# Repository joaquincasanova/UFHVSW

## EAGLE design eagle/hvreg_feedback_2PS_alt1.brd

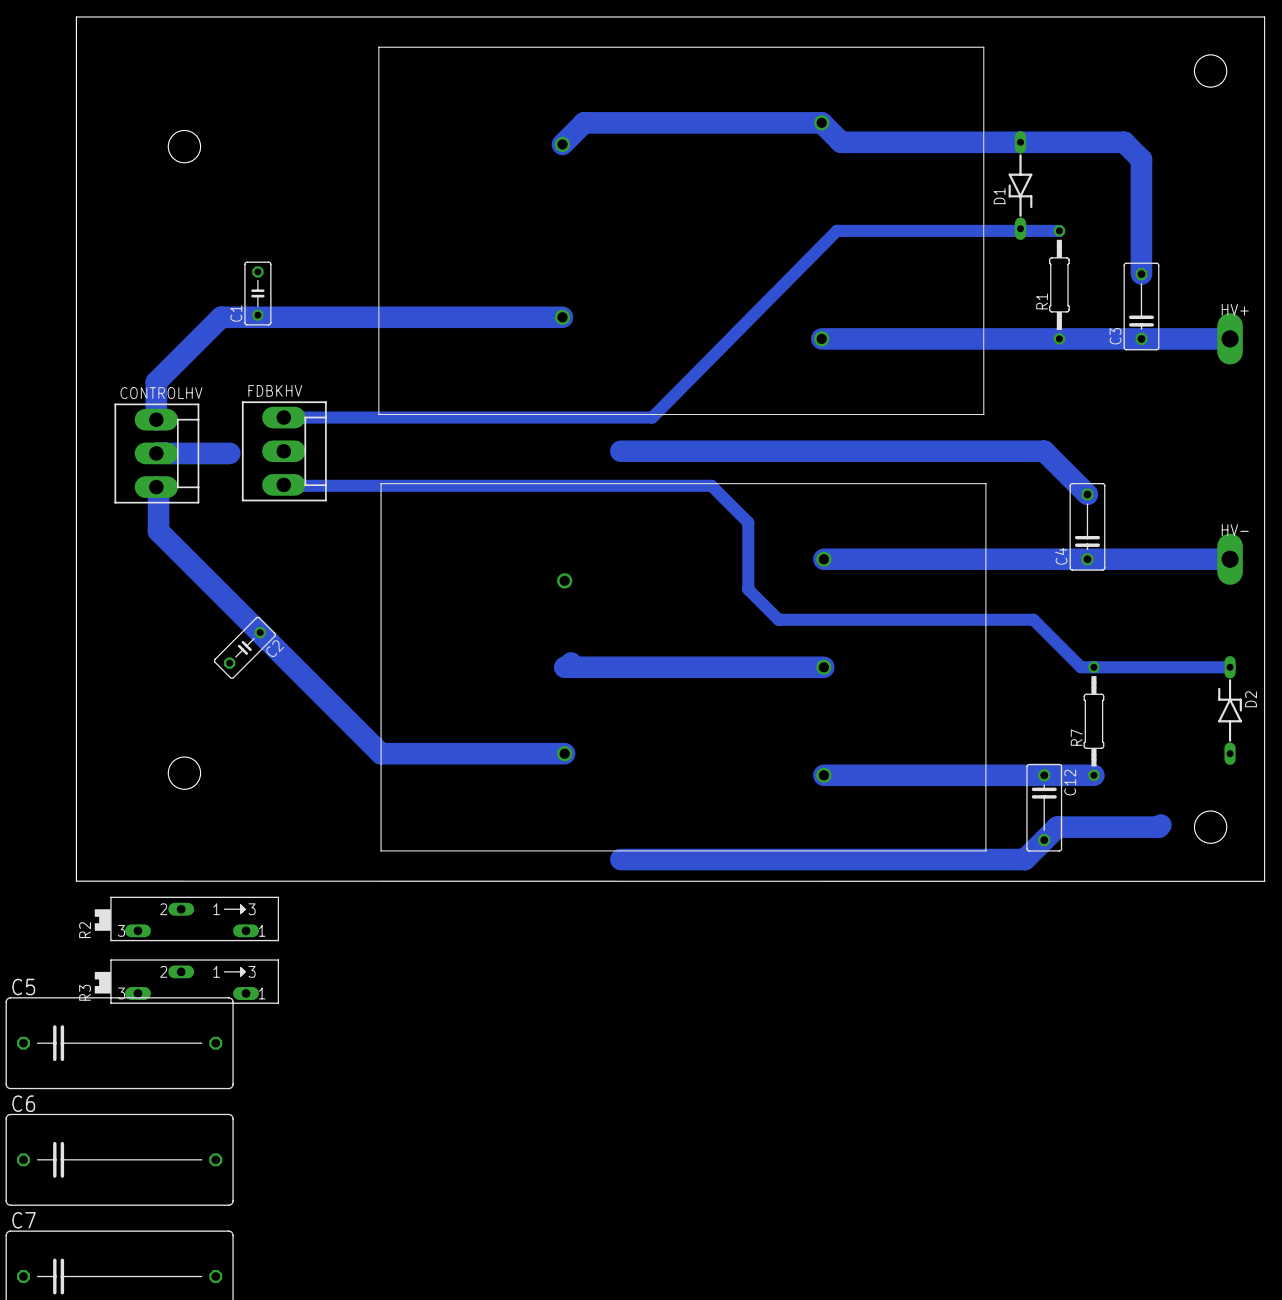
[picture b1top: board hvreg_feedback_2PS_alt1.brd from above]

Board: 2 copper layers, 139.7 x 101.6 mm, 20 parts (0 on the bottom side), 8 nets.

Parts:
C1, C2: C050-030X075
C3, C4, C12: .01u; C075-042X103
C5, C6, C7: 1u; C225-108X268
CONTROLHV: KK-156-3
D1, D2: 1n4733; ZDIO-10
FDBKHV: KK-156-3
HV+: TPPAD1-20Y; P1-20Y
HV-: TPPAD1-20Y; P1-20Y
R1, R7: 2M; 0207/12
R2, R3: SP19L
U$1: EMCO-F104PIN; EMCO-F
U$2: EMCO-F20CT; EMCO-F*CT

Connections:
GND: C1.2, C2.2, C3.2, C4.2, C5.2, C6.2, C7.2, C12.2, CONTROLHV.2, D1.A, D2.A, FDBKHV.2, R2.E, R2.S, R3.E, R3.S, U$1.P$2, U$1.P$4, U$2.P$2, U$2.P$5
unnamed: C3.1, C5.1, HV+.TP, R1.1, U$1.P$3
unnamed: C6.1, C12.1, R7.1, U$2.P$3
unnamed: D1.C, FDBKHV.1, R1.2, R2.A
unnamed: C1.1, CONTROLHV.1, U$1.P$1
unnamed: C2.1, CONTROLHV.3, U$2.P$1
unnamed: C4.1, C7.1, HV-.TP, U$2.P$4
unnamed: D2.C, FDBKHV.3, R3.A, R7.2

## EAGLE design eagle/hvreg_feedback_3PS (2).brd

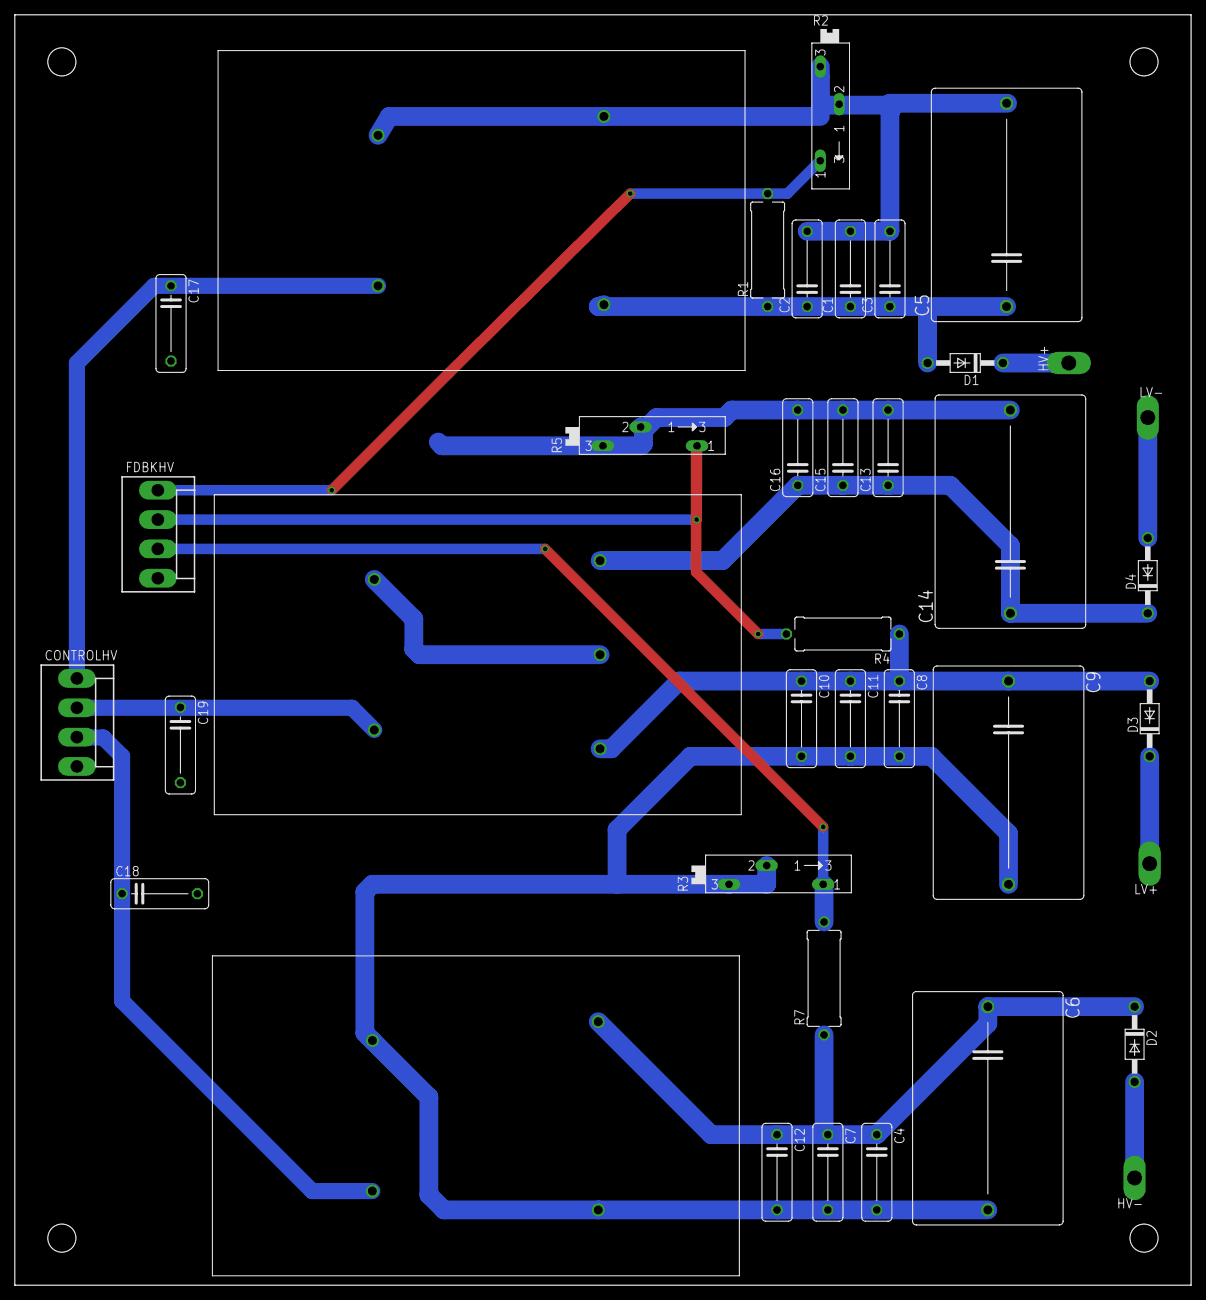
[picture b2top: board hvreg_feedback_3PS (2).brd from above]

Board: 2 copper layers, 158.8 x 171.4 mm, 38 parts (0 on the bottom side), 15 nets.

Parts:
C1, C4, C10, C15: 1n; C102-043X133
C2, C7, C11, C16: 10p; C102-043X133
C3, C8, C12, C13: .01u; C102-043X133
C5, C6, C9, C14: 1u; C275-205X316
C17, C18, C19: .1u; C102-043X133
CONTROLHV: KK-156-4
D1, D2, D3, D4: 1N4004; DO41-10
FDBKHV: KK-156-4
HV+: TPPAD1-20Y; P1-20Y
HV-: TPPAD1-20Y; P1-20Y
LV+: TPPAD1-20Y; P1-20Y
LV-: TPPAD1-20Y; P1-20Y
R1, R4, R7: 2M; P0613/15
R2, R3, R5: SP19L
U$1, U$2: EMCO-F104PIN; EMCO-F
U$3: EMCO-F20CT; EMCO-F*CT

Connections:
GND: C1.2, C2.2, C3.2, C4.2, C5.2, C6.2, C7.2, C8.2, C9.2, C10.2, C11.2, C12.2, C13.2, C14.2, C15.2, C16.2, C17.2, C18.2, C19.2, CONTROLHV.4, FDBKHV.4, R2.E, R2.S, R3.E, R3.S, R5.E, R5.S, U$1.P$2, U$1.P$4, U$2.P$2, U$2.P$3, U$3.P$2, U$3.P$5
unnamed: C1.1, C2.1, C3.1, C5.1, D1.A, R1.1, U$1.P$3
unnamed: C4.1, C6.1, C7.1, C12.1, D2.C, R7.1, U$2.P$4
unnamed: FDBKHV.1, R1.2, R2.A
unnamed: D2.A, HV-.TP
unnamed: C8.1, C9.1, C10.1, C11.1, D3.A, R4.1, U$3.P$3
unnamed: D1.C, HV+.TP
unnamed: FDBKHV.2, R4.2, R5.A
unnamed: FDBKHV.3, R3.A, R7.2
unnamed: D3.C, LV+.TP
unnamed: C13.1, C14.1, C15.1, C16.1, D4.C, U$3.P$4
unnamed: D4.A, LV-.TP
unnamed: C17.1, CONTROLHV.1, U$1.P$1
unnamed: C19.1, CONTROLHV.2, U$3.P$1
unnamed: C18.1, CONTROLHV.3, U$2.P$1

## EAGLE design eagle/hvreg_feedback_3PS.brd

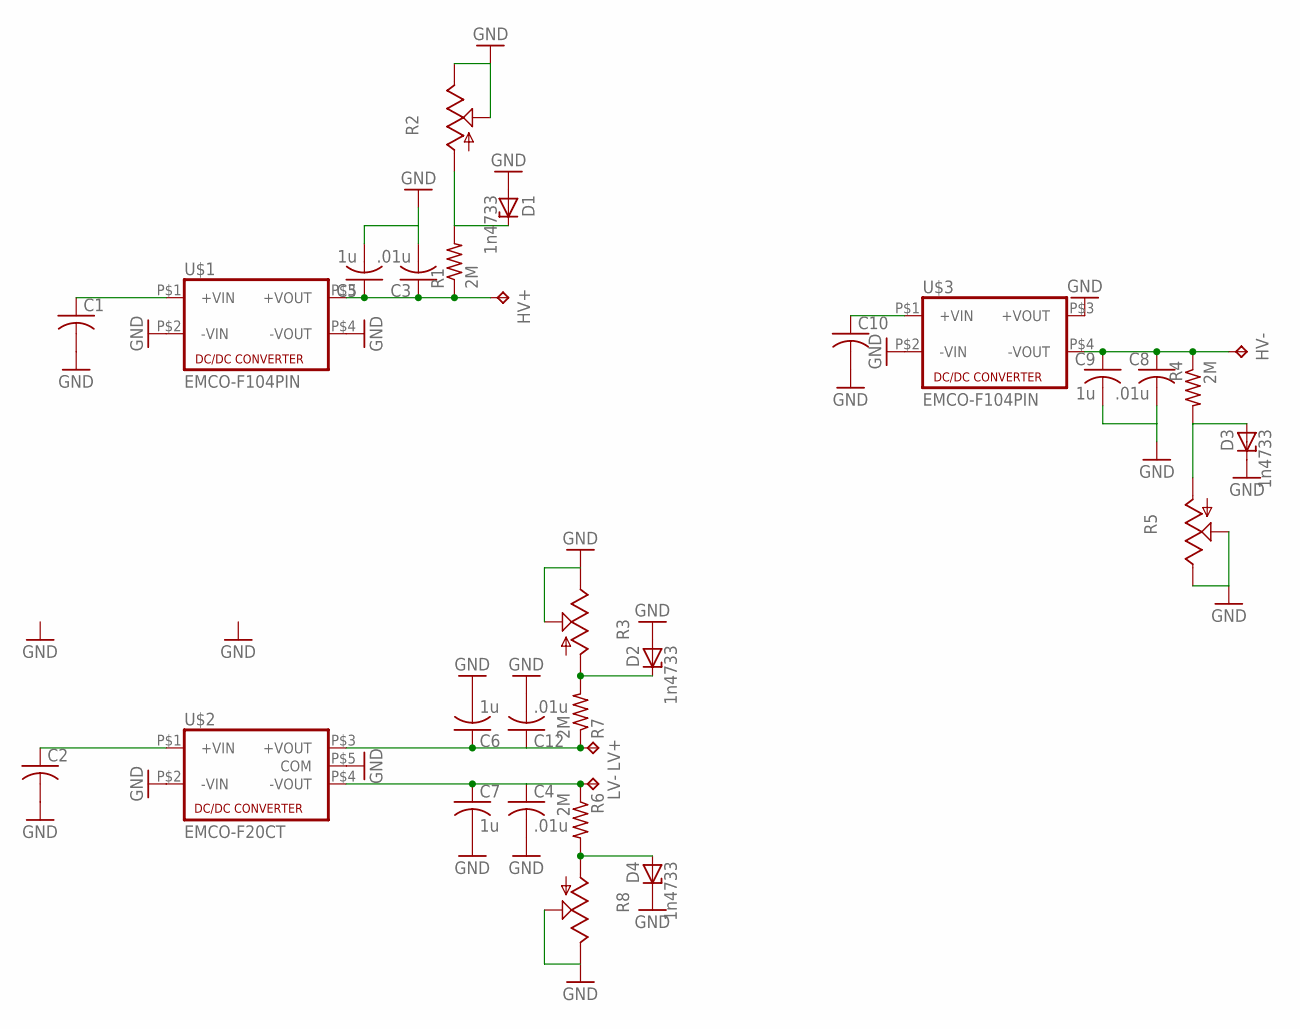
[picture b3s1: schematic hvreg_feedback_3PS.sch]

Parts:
C1, C2, C10: C-US050-030X075; C050-030X075
C3, C4, C8, C12: .01u; C075-042X103
C5, C6, C7, C9: 1u; C225-108X268
D1, D2, D3, D4: 1n4733; ZDIO-10
HV+: TPPAD1-20Y; P1-20Y
HV-: TPPAD1-20Y; P1-20Y
LV+: TPPAD1-20Y; P1-20Y
LV-: TPPAD1-20Y; P1-20Y
R1, R4, R6, R7: 2M; 0207/12
R2, R3, R5, R8: TRIM_US-B90P; SP19L
U$1, U$3: EMCO-F104PIN; EMCO-F
U$2: EMCO-F20CT; EMCO-F*CT

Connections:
GND: C1.2, C2.2, C3.2, C4.2, C5.2, C6.2, C7.2, C8.2, C9.2, C10.2, C12.2, D1.A, D2.A, D3.C, D4.C, R2.E, R2.S, R3.E, R3.S, R5.E, R5.S, R8.E, R8.S, U$1.P$2 (-VIN), U$1.P$4 (-VOUT), U$2.P$2 (-VIN), U$2.P$5 (COM), U$3.P$2 (-VIN), U$3.P$3 (+VOUT)
unnamed: C3.1, C5.1, HV+.TP, R1.1, U$1.P$3 (+VOUT)
unnamed: C6.1, C12.1, LV+.TP, R7.1, U$2.P$3 (+VOUT)
unnamed: D1.C, R1.2, R2.A
unnamed: C1.1, U$1.P$1 (+VIN)
unnamed: C2.1, U$2.P$1 (+VIN)
unnamed: C4.1, C7.1, LV-.TP, R6.1
unnamed: C8.1, C9.1, HV-.TP, R4.1
unnamed: D2.C, R3.A, R7.2
unnamed: D3.A, R4.2, R5.A
unnamed: C10.1, U$3.P$1 (+VIN)
unnamed: D4.A, R6.2, R8.A

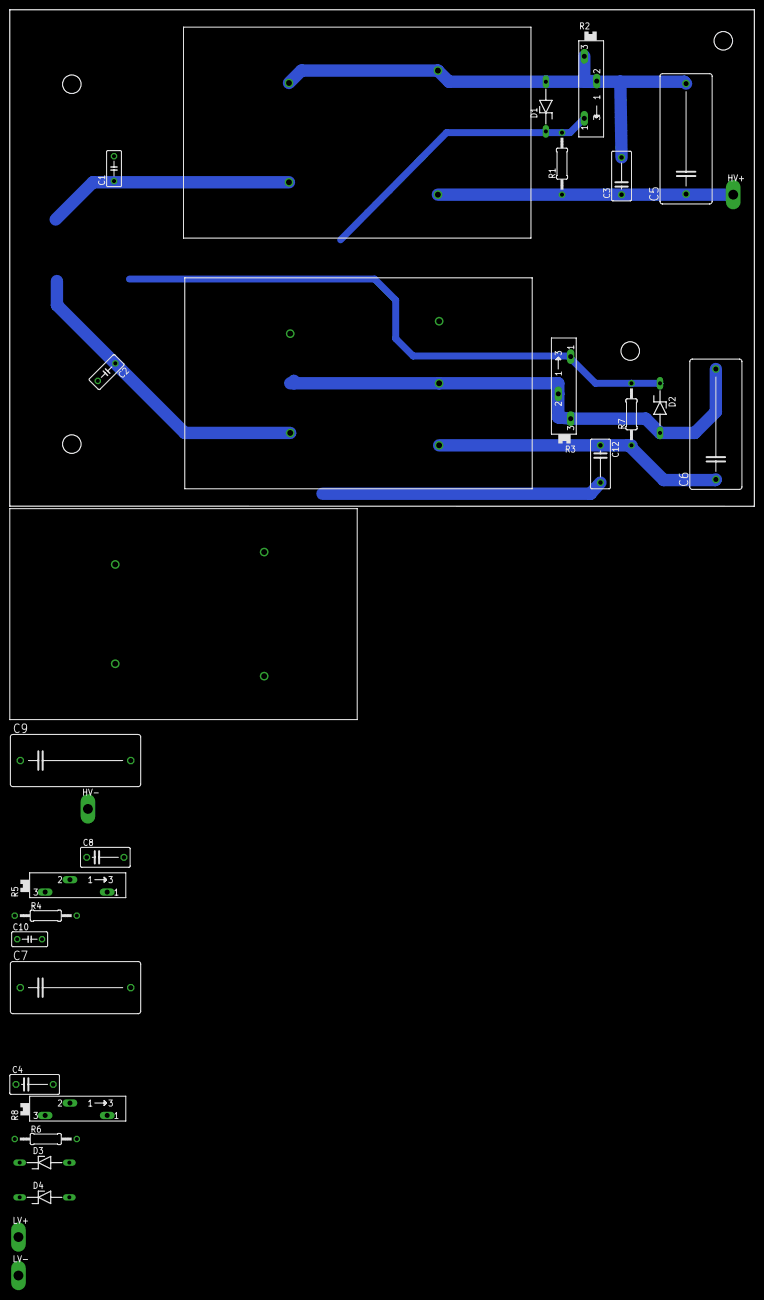
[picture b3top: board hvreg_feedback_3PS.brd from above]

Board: 2 copper layers, 152.4 x 101.6 mm, 30 parts (0 on the bottom side), 12 nets.

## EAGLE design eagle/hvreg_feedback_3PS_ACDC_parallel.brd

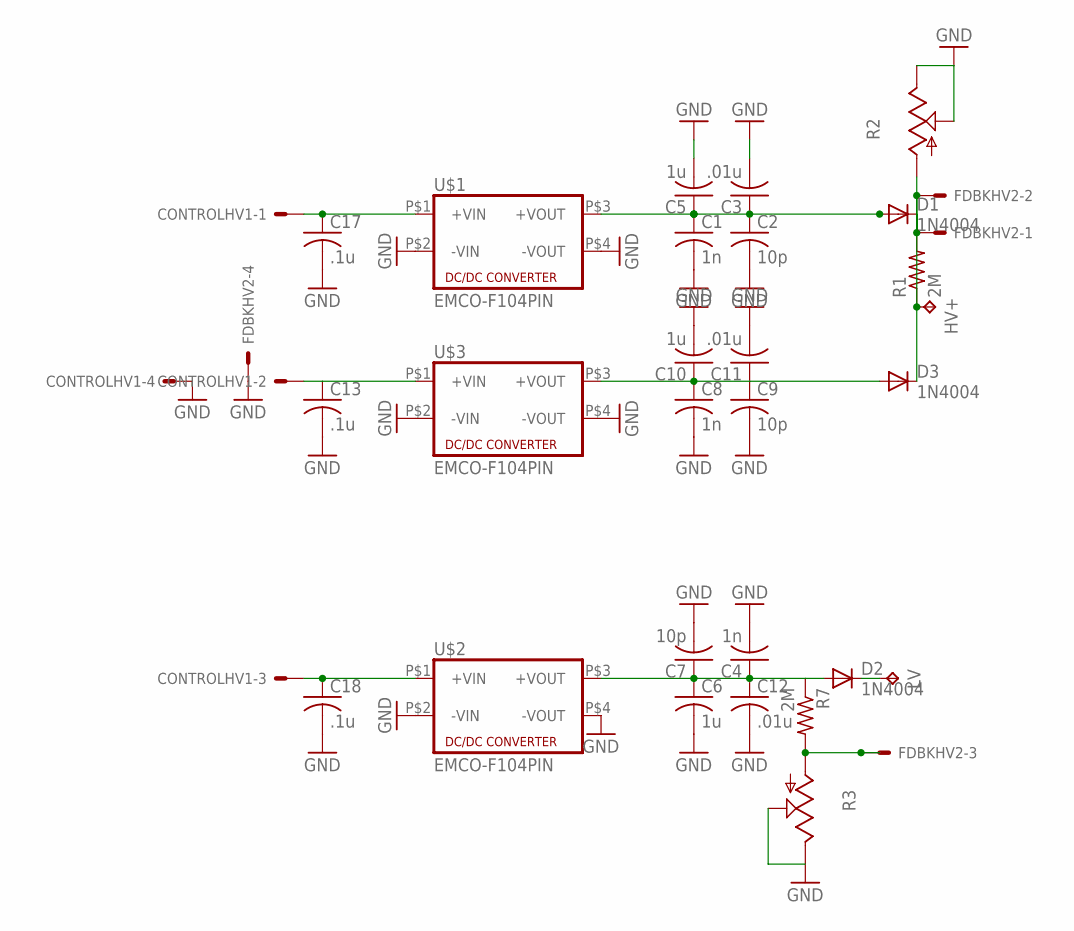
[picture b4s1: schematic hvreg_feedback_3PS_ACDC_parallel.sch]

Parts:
C1, C4, C8: 1n; C102-043X133
C2, C7, C9: 10p; C102-043X133
C3, C11, C12: .01u; C102-043X133
C5, C6, C10: 1u; C275-205X316
C13, C17, C18: .1u; C102-043X133
CONTROLHV1: KK-156-4
D1, D2, D3: 1N4004; DO41-10
FDBKHV2: KK-156-4
HV+: TPPAD1-20Y; P1-20Y
LV: TPPAD1-20Y; P1-20Y
R1, R7: 2M; P0613/15
R2, R3: TRIM_US-B90P; SP19L
U$1, U$2, U$3: EMCO-F104PIN; EMCO-F

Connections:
GND: C1.2, C2.2, C3.2, C4.2, C5.2, C6.2, C7.2, C8.2, C9.2, C10.2, C11.2, C12.2, C13.2, C17.2, C18.2, CONTROLHV1.4, FDBKHV2.4, R2.E, R2.S, R3.E, R3.S, U$1.P$2 (-VIN), U$1.P$4 (-VOUT), U$2.P$2 (-VIN), U$2.P$4 (-VOUT), U$3.P$2 (-VIN), U$3.P$4 (-VOUT)
unnamed: C1.1, C2.1, C3.1, C5.1, D1.A, U$1.P$3 (+VOUT)
unnamed: C4.1, C6.1, C7.1, C12.1, D2.A, R7.1, U$2.P$3 (+VOUT)
unnamed: FDBKHV2.1, FDBKHV2.2, R1.2, R2.A
unnamed: D2.C, LV.TP
unnamed: D1.C, D3.C, HV+.TP, R1.1
unnamed: C8.1, C9.1, C10.1, C11.1, D3.A, U$3.P$3 (+VOUT)
unnamed: FDBKHV2.3, R3.A, R7.2
unnamed: C13.1, CONTROLHV1.2, U$3.P$1 (+VIN)
unnamed: C17.1, CONTROLHV1.1, U$1.P$1 (+VIN)
unnamed: C18.1, CONTROLHV1.3, U$2.P$1 (+VIN)

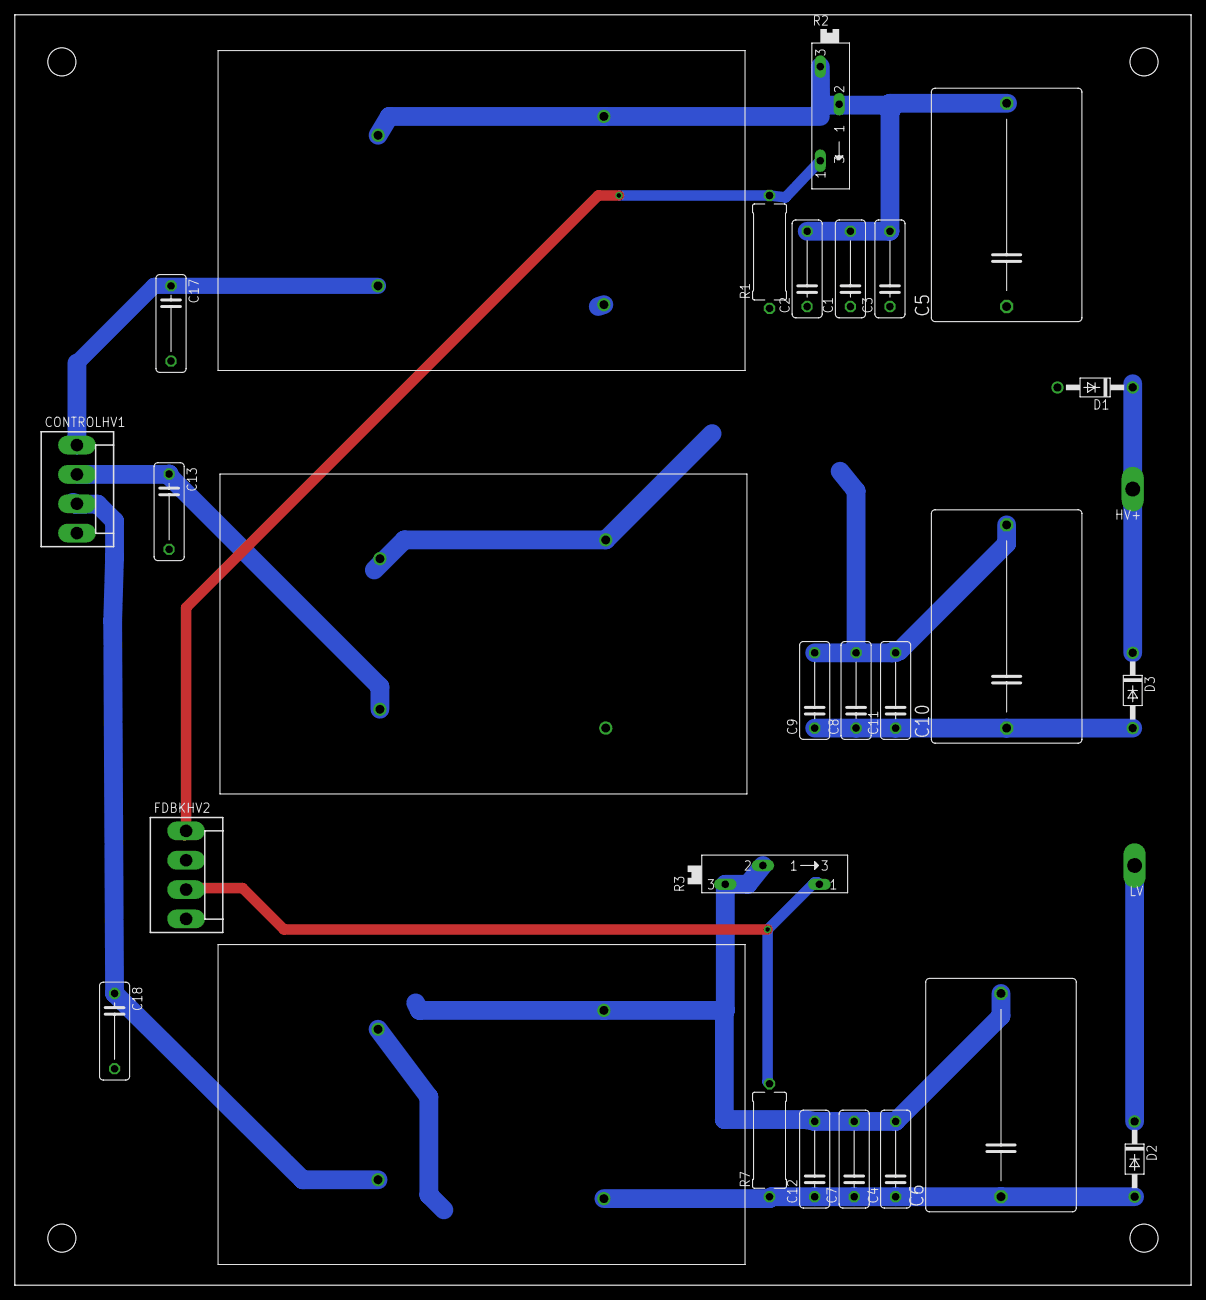
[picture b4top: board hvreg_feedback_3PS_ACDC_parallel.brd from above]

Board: 2 copper layers, 158.8 x 171.4 mm, 29 parts (0 on the bottom side), 11 nets.

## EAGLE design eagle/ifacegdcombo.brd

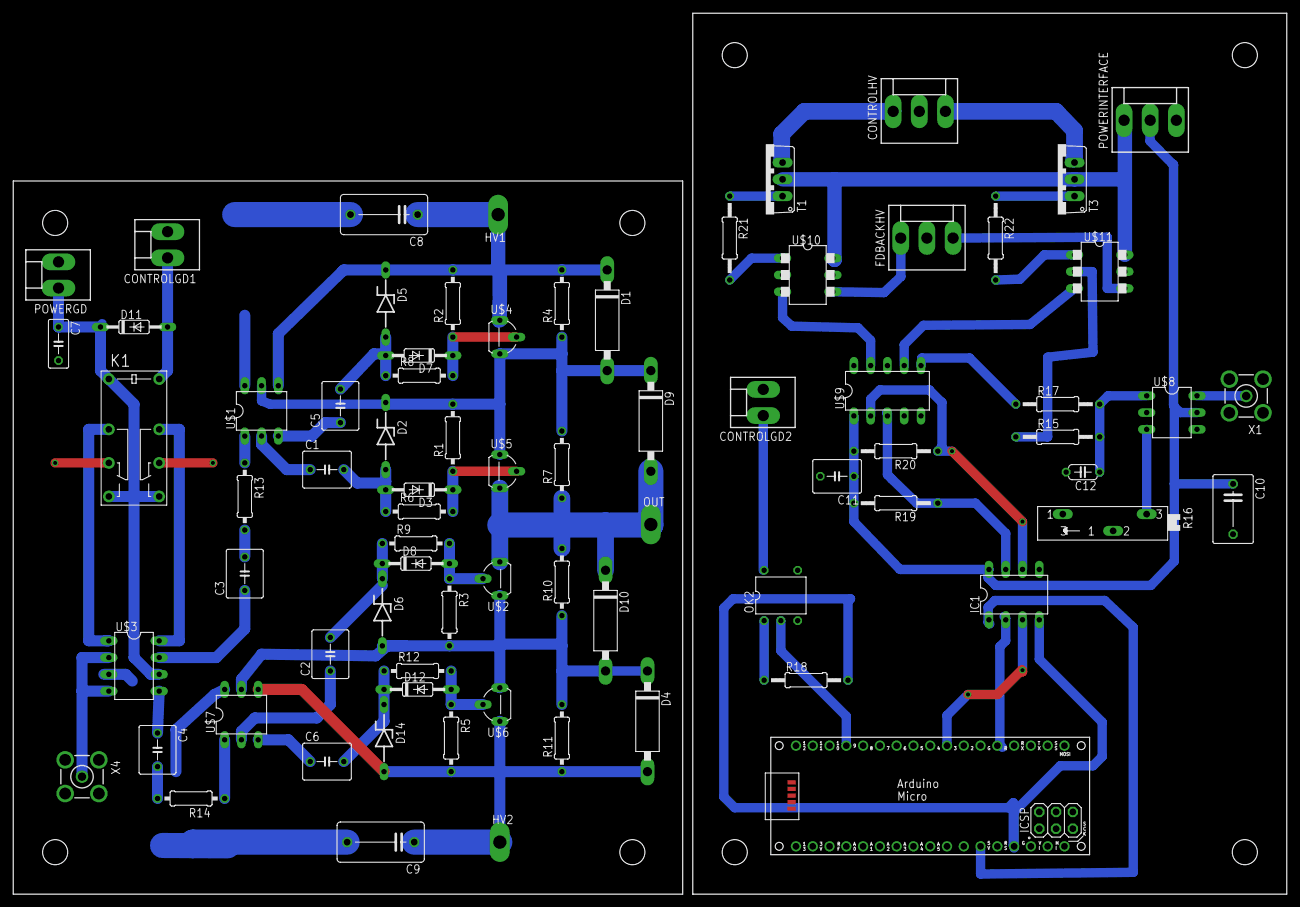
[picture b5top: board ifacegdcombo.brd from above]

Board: 2 copper layers, 192.8 x 133.3 mm, 75 parts (0 on the bottom side), 55 nets.

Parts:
C1, C2, C3, C4, C5, C6: .22u; C050-055X075
C7: C050-030X075
C8, C9: 10p; C102-064X133
C10: C075-063X106
C11: C050-050X075
C12: 10n; C050-024X044
CONTROLGD1, CONTROLGD2: KK-156-2
CONTROLHV: KK-156-3
D1, D4, D9, D10: P6KEXXA; C1702-15
D2, D5, D6, D14: 4742; ZDIO-10
D3, D7, D8, D11, D12: 1N4148DO35-10; DO35-10
FDBACKHV: KK-156-3
HV1, HV2: TPPAD1-20Y; P1-20Y
IC1: ISO1540; DIL08
K1: G5V-2
OK2: H11F1; DIL05
OUT: TPPAD1-20Y; P1-20Y
PCB1: ARDUINO_MICRO
POWERGD: KK-156-2
POWERINTERFACE: KK-156-3
R1, R2, R3, R5: 50k; 0207/10
R4, R7, R10, R11, R14: 1M; 0207/10
R6, R8, R9, R12, R13: 70; 0207/10
R15: 10k; 0207/12
R16: SP19L
R17: 40k; 0207/12
R18: 100; 0207/12
R19, R20: 1.5k; 0207/12
R21, R22: 1k; 0207/12
T1, T3: TIP122V; TO220V
U$1, U$7: DA-2320; DIL06
U$2, U$6: VN0550L; TO92L
U$3: UCC27425; DIL08
U$4, U$5: VP0550L; TO92L
U$8: LTC6992; DIL06
U$9: MCP4728DIL; DIL10
U$10, U$11: MAX9650DIL; DIL06-4
X1, X4: BU-SMA-V

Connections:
+12V: POWERINTERFACE.1, T1.2, T3.2, U$10.6, U$11.6
+15V: C7.1, D11.C, K1.1, K1.8, K1.9, POWERGD.1, U$3.6
A+5: IC1.1, PCB1.+5V
AGND: IC1.4, PCB1.GND., R18.2
ENSW: CONTROLGD1.1, D11.A, K1.16
ENSW2: CONTROLGD2.1, OK2.6
GND: C7.2, C8.2, C9.2, CONTROLGD1.2, K1.6, K1.11, POWERGD.2, U$1.6, U$3.3, U$7.6, X4.2, X4.3, X4.4, X4.5
GND1: C10.2, C11.2, C12.2, CONTROLGD2.2, CONTROLHV.2, FDBACKHV.2, IC1.5, OK2.4, POWERINTERFACE.3, R15.1, R16.A, R16.S, U$8.DIV, U$8.GND, U$9.4, U$9.10, U$10.2, U$11.2, X1.2, X1.3, X1.4, X1.5
unnamed: U$3.2, U$3.4, X4.1
unnamed: C3.1, U$3.7
unnamed: R13.1, U$1.1
unnamed: C4.1, U$3.5
unnamed: C1.1, U$1.2
unnamed: R14.1, U$7.1
unnamed: C5.1, U$1.3
unnamed: D3.C, R1.1, R6.2, U$5.2
unnamed: C1.2, D2.A, D3.A, R6.1
unnamed: D12.A, R5.1, R12.2, U$6.2
unnamed: D7.C, R2.1, R8.2, U$4.2
unnamed: D4.C, D6.A, D10.A, R3.2, R10.1, R11.2, U$2.3, U$6.1
unnamed: K1.4, U$3.1
unnamed: K1.13, U$3.8
unnamed: C5.2, D5.A, D7.A, R8.1
unnamed: C8.1, D1.C, D5.C, HV1.TP, R2.2, R4.2, U$1.4, U$4.3
unnamed: D1.A, D2.C, D9.C, R1.2, R4.1, R7.2, U$1.5, U$4.1, U$5.3
unnamed: C3.2, R13.2
unnamed: C4.2, R14.2
unnamed: D9.A, D10.C, OUT.TP, R7.1, R10.2, U$2.1, U$5.1
unnamed: C2.1, U$7.2
unnamed: C6.1, U$7.3
unnamed: C9.1, D4.A, D14.A, HV2.TP, R5.2, R11.1, U$6.3, U$7.4
unnamed: C2.2, D6.C, D8.C, R9.1
unnamed: R16.E, U$8.SET
unnamed: C6.2, D12.C, D14.C, R12.1
unnamed: U$8.OUT, X1.1
unnamed: OK2.1, R18.1
unnamed: C12.1, R15.2, R17.2, U$8.MOD
unnamed: FDBACKHV.1, U$10.4
unnamed: FDBACKHV.3, U$11.4
unnamed: U$9.9, U$10.3
unnamed: U$9.7, U$11.3
unnamed: R17.1, U$9.6
unnamed: R22.1, T3.1
unnamed: R21.2, U$10.1
unnamed: R22.2, U$11.1
unnamed: CONTROLHV.1, T1.3
unnamed: CONTROLHV.3, T3.3
unnamed: R21.1, T1.1
unnamed: D8.A, R3.1, R9.2, U$2.2
PWM9: OK2.2, PCB1.D9
SCL: IC1.3, PCB1.D3
SCL_OUT: IC1.6, R20.1, U$9.2
SDA: IC1.2, PCB1.D2
SDA_OUT: IC1.7, R19.1, U$9.3
VCC: C10.1, C11.1, IC1.8, POWERINTERFACE.2, R19.2, R20.2, U$8.VCC, U$9.1

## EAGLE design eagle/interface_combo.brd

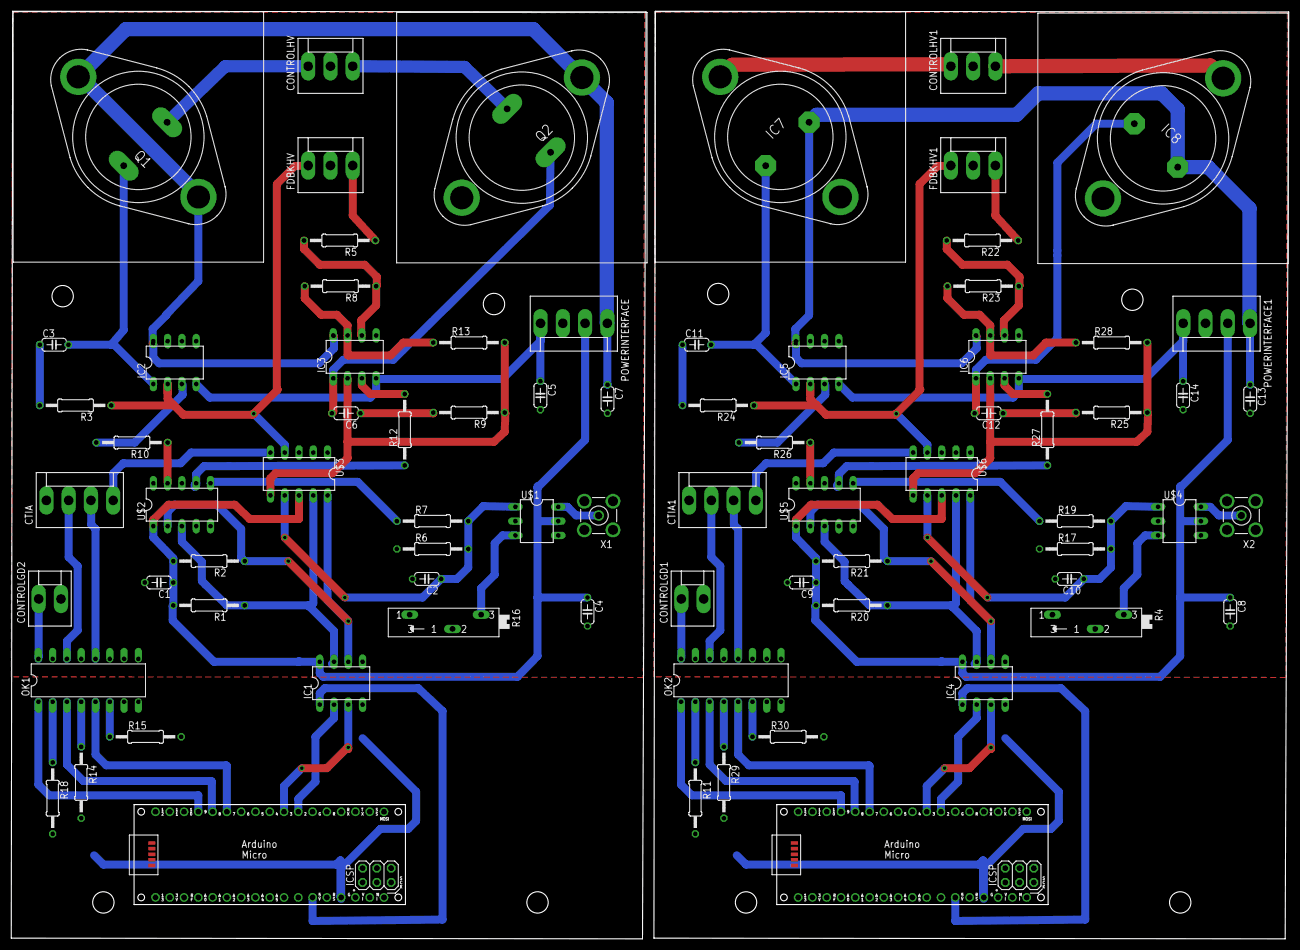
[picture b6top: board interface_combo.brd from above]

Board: 2 copper layers, 227.2 x 165.0 mm, 76 parts (0 on the bottom side), 78 nets.

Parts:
C1, C2, C3, C4, C5, C6, C7, C8, C9, C10, C11, C12, C13, C14: 10n; C050-024X044
CONTROLGD1, CONTROLGD2: KK-156-2
CONTROLHV, CONTROLHV1: KK-156-3
CTIA, CTIA1: KK-156-4
FDBKHV, FDBKHV1: KK-156-3
IC1, IC4: ISO1540; DIL08
IC2, IC3, IC5, IC6: LT1352PA; DIL08
IC7, IC8: TO3-K02
OK1, OK2: PS2501"; DIL16
PCB1, PCB2: ARDUINO_MICRO
POWERINTERFACE, POWERINTERFACE1: KK-156-4
Q1, Q2: 2N3055; TO3
R1, R2, R20, R21: 1.5k; 0207/12
R3, R6, R9, R10, R12, R13, R17, R24, R25, R26, R27, R28: 10k; 0207/12
R4, R16: 100k; SP19L
R5, R8, R22, R23: 20k; 0207/12
R7, R19: 40k; 0207/12
R11, R14, R15, R18, R29, R30: 100; 0207/12
U$1, U$4: LTC6992; DIL06
U$2, U$5: MCP4728DIL; DIL10
U$3, U$6: ADS1015DIL; DIL10
X1, X2: BU-SMA-V

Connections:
+15V: C7.1, IC2.8, IC3.8, POWERINTERFACE.1, Q1.C, Q1.C/, Q2.C, Q2.C/
+15V1: C13.1, IC5.8, IC6.8, IC7.1, IC8.1, POWERINTERFACE1.1
-15V: C5.1, IC2.4, IC3.4, POWERINTERFACE.4
-15V1: C14.1, IC5.4, IC6.4, POWERINTERFACE1.4
A+1: IC4.1, PCB2.+5V
A+5: IC1.1, PCB1.+5V
AGND: IC1.4, PCB1.GND., R14.2, R15.2, R18.2
AGND1: IC4.4, PCB2.GND., R11.2, R29.2, R30.2
CTIA: CTIA.4, U$3.5
CTIA1: CTIA1.4, U$6.5
D1: OK2.5, PCB2.D7
D2: OK2.3, PCB2.D8
D7: OK1.5, PCB1.D7
D8: OK1.3, PCB1.D8
ENSW1: CONTROLGD1.1, OK2.16
ENSW2: CONTROLGD2.1, OK1.16
GND: C1.2, C2.2, C4.2, C5.2, C7.2, CONTROLGD2.2, CONTROLHV.2, CTIA.1, FDBKHV.2, IC1.5, IC3.5, OK1.11, OK1.13, OK1.15, POWERINTERFACE.3, R6.1, R16.A, R16.S, U$1.DIV, U$1.GND, U$2.4, U$2.10, U$3.1, U$3.3, X1.2, X1.3, X1.4, X1.5
GND1: C8.2, C9.2, C10.2, C13.2, C14.2, CONTROLGD1.2, CONTROLHV1.2, CTIA1.1, FDBKHV1.2, IC4.5, IC6.5, OK2.11, OK2.13, OK2.15, POWERINTERFACE1.3, R4.A, R4.S, R17.1, U$4.DIV, U$4.GND, U$5.4, U$5.10, U$6.1, U$6.3, X2.2, X2.3, X2.4, X2.5
unnamed: R7.1, U$2.6
unnamed: OK1.4, R14.1
unnamed: C3.1, R3.2
unnamed: CONTROLHV.1, Q1.E
unnamed: CONTROLHV.3, Q2.E
unnamed: OK1.6, R15.1
unnamed: OK1.2, R18.1
unnamed: FDBKHV.3, R5.1
unnamed: R4.E, U$4.SET
unnamed: U$4.OUT, X2.1
unnamed: IC6.7, R23.2, R28.1
unnamed: R16.E, U$1.SET
unnamed: U$1.OUT, X1.1
unnamed: IC3.7, R8.2, R13.1
unnamed: IC6.3, R27.2
unnamed: IC2.3, R10.2
unnamed: R19.1, U$5.6
unnamed: IC3.3, R12.2
unnamed: C3.2, IC2.1, Q1.B
unnamed: C6.1, R9.2
unnamed: C6.2, IC3.1, Q2.B
unnamed: IC3.6, R5.2, R8.1
unnamed: R10.1, U$2.9
unnamed: R12.1, U$2.7
unnamed: C11.2, IC5.1, IC7.2
unnamed: IC6.6, R22.2, R23.1
unnamed: C12.2, IC6.1, IC8.2
unnamed: C11.1, R24.2
unnamed: C12.1, R25.2
unnamed: IC5.3, R26.2
unnamed: R26.1, U$5.9
unnamed: R27.1, U$5.7
unnamed: OK2.4, R29.1
unnamed: OK2.6, R30.1
unnamed: OK2.2, R11.1
unnamed: CONTROLHV1.1, IC7.3
unnamed: CONTROLHV1.3, IC8.3
unnamed: FDBKHV1.3, R22.1
PWM3: OK2.1, PCB2.D9
PWM9: OK1.1, PCB1.D9
RDBK1: FDBKHV.1, IC2.2, R3.1, U$3.4
RDBK2: FDBKHV1.1, IC5.2, R24.1, U$6.4
RDBK3: IC3.2, R9.1, R13.2, U$3.6
RDBK4: C2.1, R6.2, R7.2, U$1.MOD, U$3.7
RDBK5: IC6.2, R25.1, R28.2, U$6.6
RDBK6: C10.1, R17.2, R19.2, U$4.MOD, U$6.7
RESET: CTIA.3, OK1.12
RESET1: CTIA1.3, OK2.12
SAMPLE: CTIA.2, OK1.14
SAMPLE1: CTIA1.2, OK2.14
SCL: IC1.3, PCB1.D3
SCL1: IC4.3, PCB2.D3
SCL_OUT: IC1.6, R2.1, U$2.2, U$3.10
SCL_OUT1: IC4.6, R21.1, U$5.2, U$6.10
SDA: IC1.2, PCB1.D2
SDA1: IC4.2, PCB2.D2
SDA_OUT: IC1.7, R1.1, U$2.3, U$3.9
SDA_OUT1: IC4.7, R20.1, U$5.3, U$6.9
VCC: C1.1, C4.1, IC1.8, POWERINTERFACE.2, R1.2, R2.2, U$1.VCC, U$2.1, U$3.8
VCC1: C8.1, C9.1, IC4.8, POWERINTERFACE1.2, R20.2, R21.2, U$4.VCC, U$5.1, U$6.8

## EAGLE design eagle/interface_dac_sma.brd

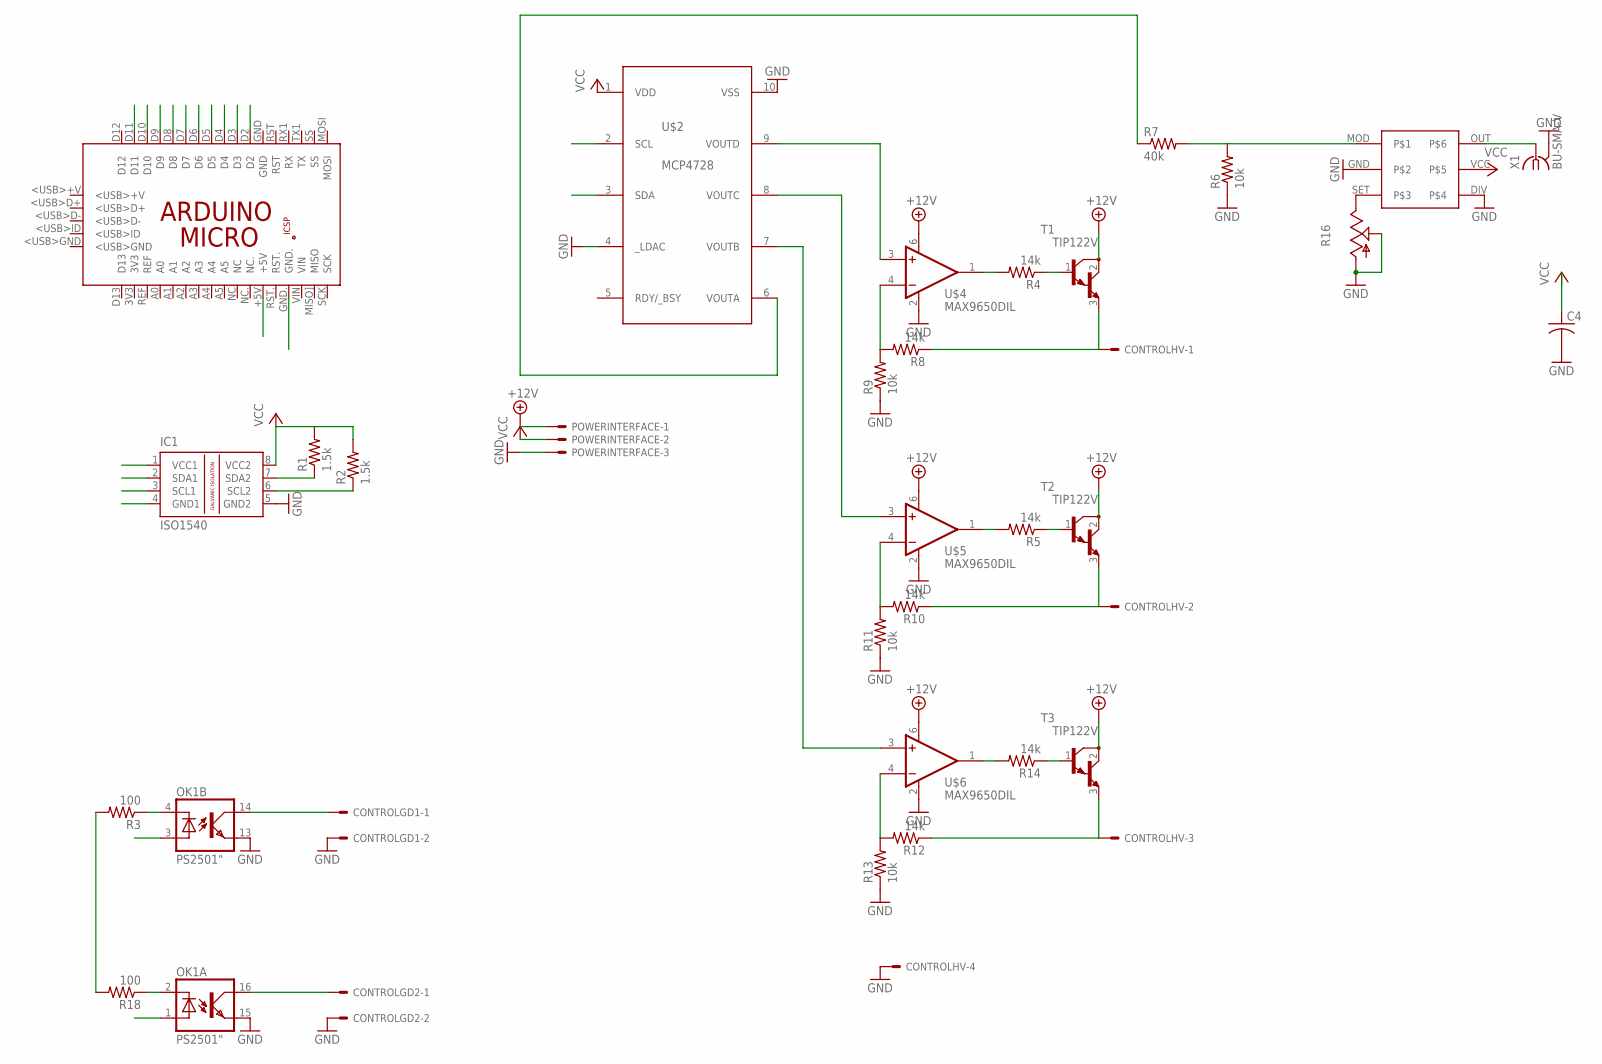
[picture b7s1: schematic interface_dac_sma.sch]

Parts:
C4: C-US075-063X106; C075-063X106
CONTROLGD1, CONTROLGD2: KK-156-2
CONTROLHV: KK-156-4
IC1: ISO1540; DIL08
OK1: PS2501"; DIL16
PCB1: ARDUINO_MICRO
POWERINTERFACE: KK-156-3
R1, R2: 1.5k; 0207/12
R3, R18: 100; 0207/12
R4, R5, R8, R10, R12, R14: 14k; 0207/12
R6, R9, R11, R13: 10k; 0207/12
R7: 40k; 0207/12
R16: TRIM_US-B90P; SP19L
T1, T2, T3: TIP122V; TO220V
U$1: LTC6992; DIL06
U$2: MCP4728DIL; DIL10
U$4, U$5, U$6: MAX9650DIL; DIL06-4
X1: BU-SMA-V

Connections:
+12V: POWERINTERFACE.1, T1.2 (C), T2.2 (C), T3.2 (C), U$4.6 (V+), U$5.6 (V+), U$6.6 (V+)
A+5: IC1.1 (VCC1), PCB1.+5V
AGND: IC1.4 (GND1), PCB1.GND., R3.2, R18.2
D4: PCB1.D4
D7: PCB1.D7
D8: PCB1.D8
D10: PCB1.D10
D11: PCB1.D11
ENSW1: CONTROLGD1.1, OK1.14 (COL)
ENSW2: CONTROLGD2.1, OK1.16 (COL)
GND: C4.2, CONTROLGD1.2, CONTROLGD2.2, CONTROLHV.4, IC1.5 (GND2), OK1.13 (EMI), OK1.15 (EMI), POWERINTERFACE.3, R6.1, R9.1, R11.1, R13.1, R16.A, R16.S, U$1.DIV, U$1.GND, U$2.4 (_LDAC), U$2.10 (VSS), U$4.2 (V-), U$5.2 (V-), U$6.2 (V-), X1.2, X1.3 (2), X1.4 (2), X1.5 (2)
unnamed: R7.1, U$2.6 (VOUTA)
unnamed: R6.2, R7.2, U$1.MOD
unnamed: R4.1, T1.1 (B)
unnamed: CONTROLHV.1, R8.1, T1.3 (E)
unnamed: R5.1, T2.1 (B)
unnamed: CONTROLHV.2, R10.1, T2.3 (E)
unnamed: OK1.2 (C), R18.1
unnamed: R8.2, R9.2, U$4.4 (-IN)
unnamed: R10.2, R11.2, U$5.4 (-IN)
unnamed: OK1.4 (C), R3.1
unnamed: CONTROLHV.3, R12.1, T3.3 (E)
unnamed: R16.E, U$1.SET
unnamed: U$1.OUT, X1.1
unnamed: R12.2, R13.2, U$6.4 (-IN)
unnamed: R14.1, T3.1 (B)
unnamed: U$2.9 (VOUTD), U$4.3 (+IN)
unnamed: U$2.8 (VOUTC), U$5.3 (+IN)
unnamed: U$2.7 (VOUTB), U$6.3 (+IN)
unnamed: R4.2, U$4.1 (OUT)
unnamed: R5.2, U$5.1 (OUT)
unnamed: R14.2, U$6.1 (OUT)
PWM5: PCB1.D5
PWM6: OK1.3 (A), PCB1.D6
PWM9: OK1.1 (A), PCB1.D9
SCL: IC1.3 (SCL1), PCB1.D3
SCL_OUT: IC1.6 (SCL2), R2.1, U$2.2 (SCL)
SDA: IC1.2 (SDA1), PCB1.D2
SDA_OUT: IC1.7 (SDA2), R1.1, U$2.3 (SDA)
VCC: C4.1, IC1.8 (VCC2), POWERINTERFACE.2, R1.2, R2.2, U$1.VCC, U$2.1 (VDD)

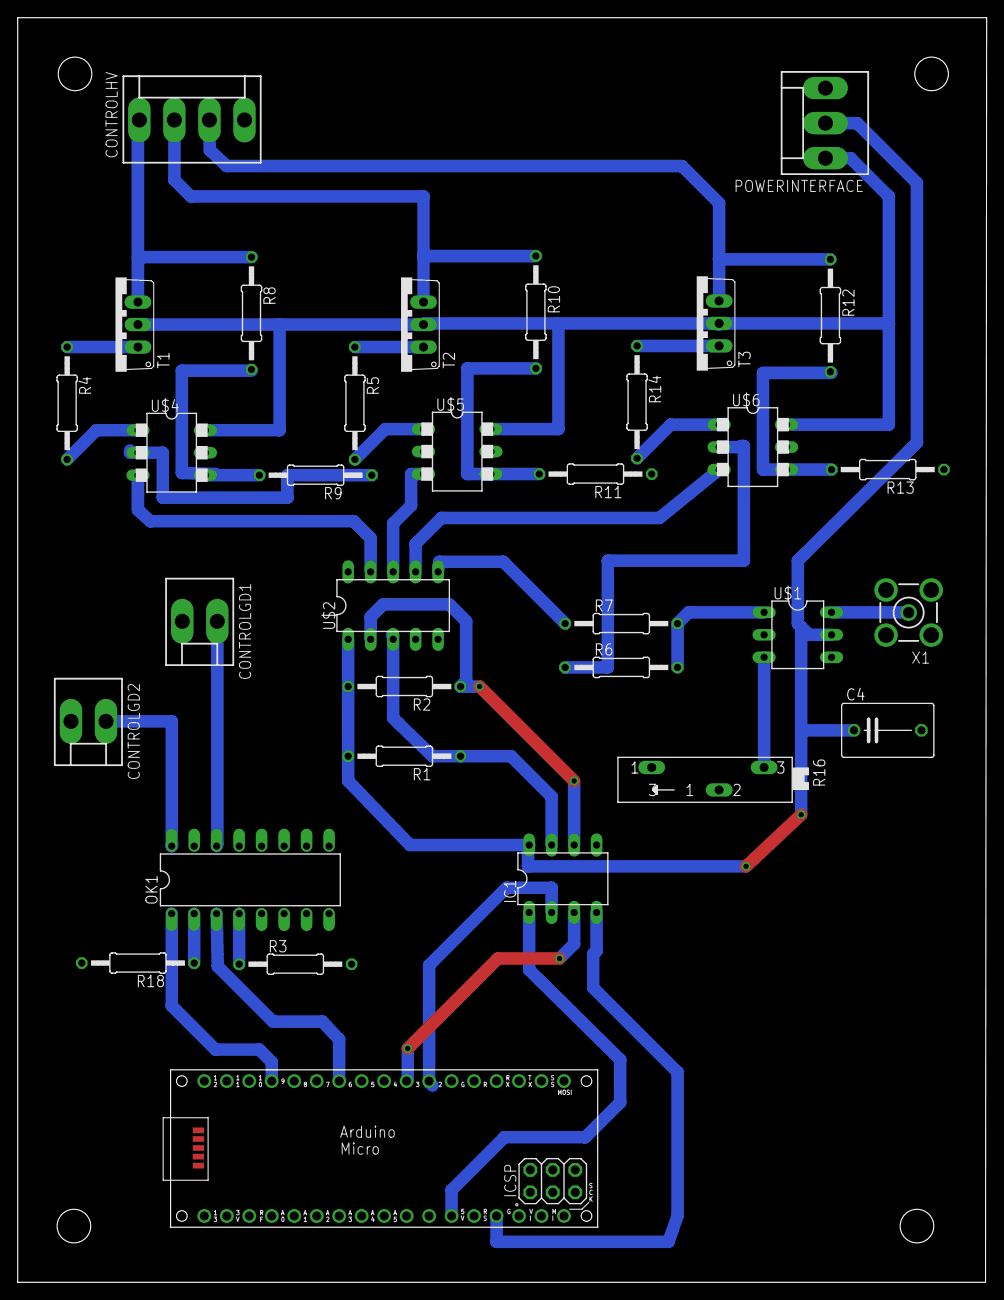
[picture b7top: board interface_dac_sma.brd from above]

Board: 2 copper layers, 109.5 x 142.9 mm, 33 parts (0 on the bottom side), 34 nets.
